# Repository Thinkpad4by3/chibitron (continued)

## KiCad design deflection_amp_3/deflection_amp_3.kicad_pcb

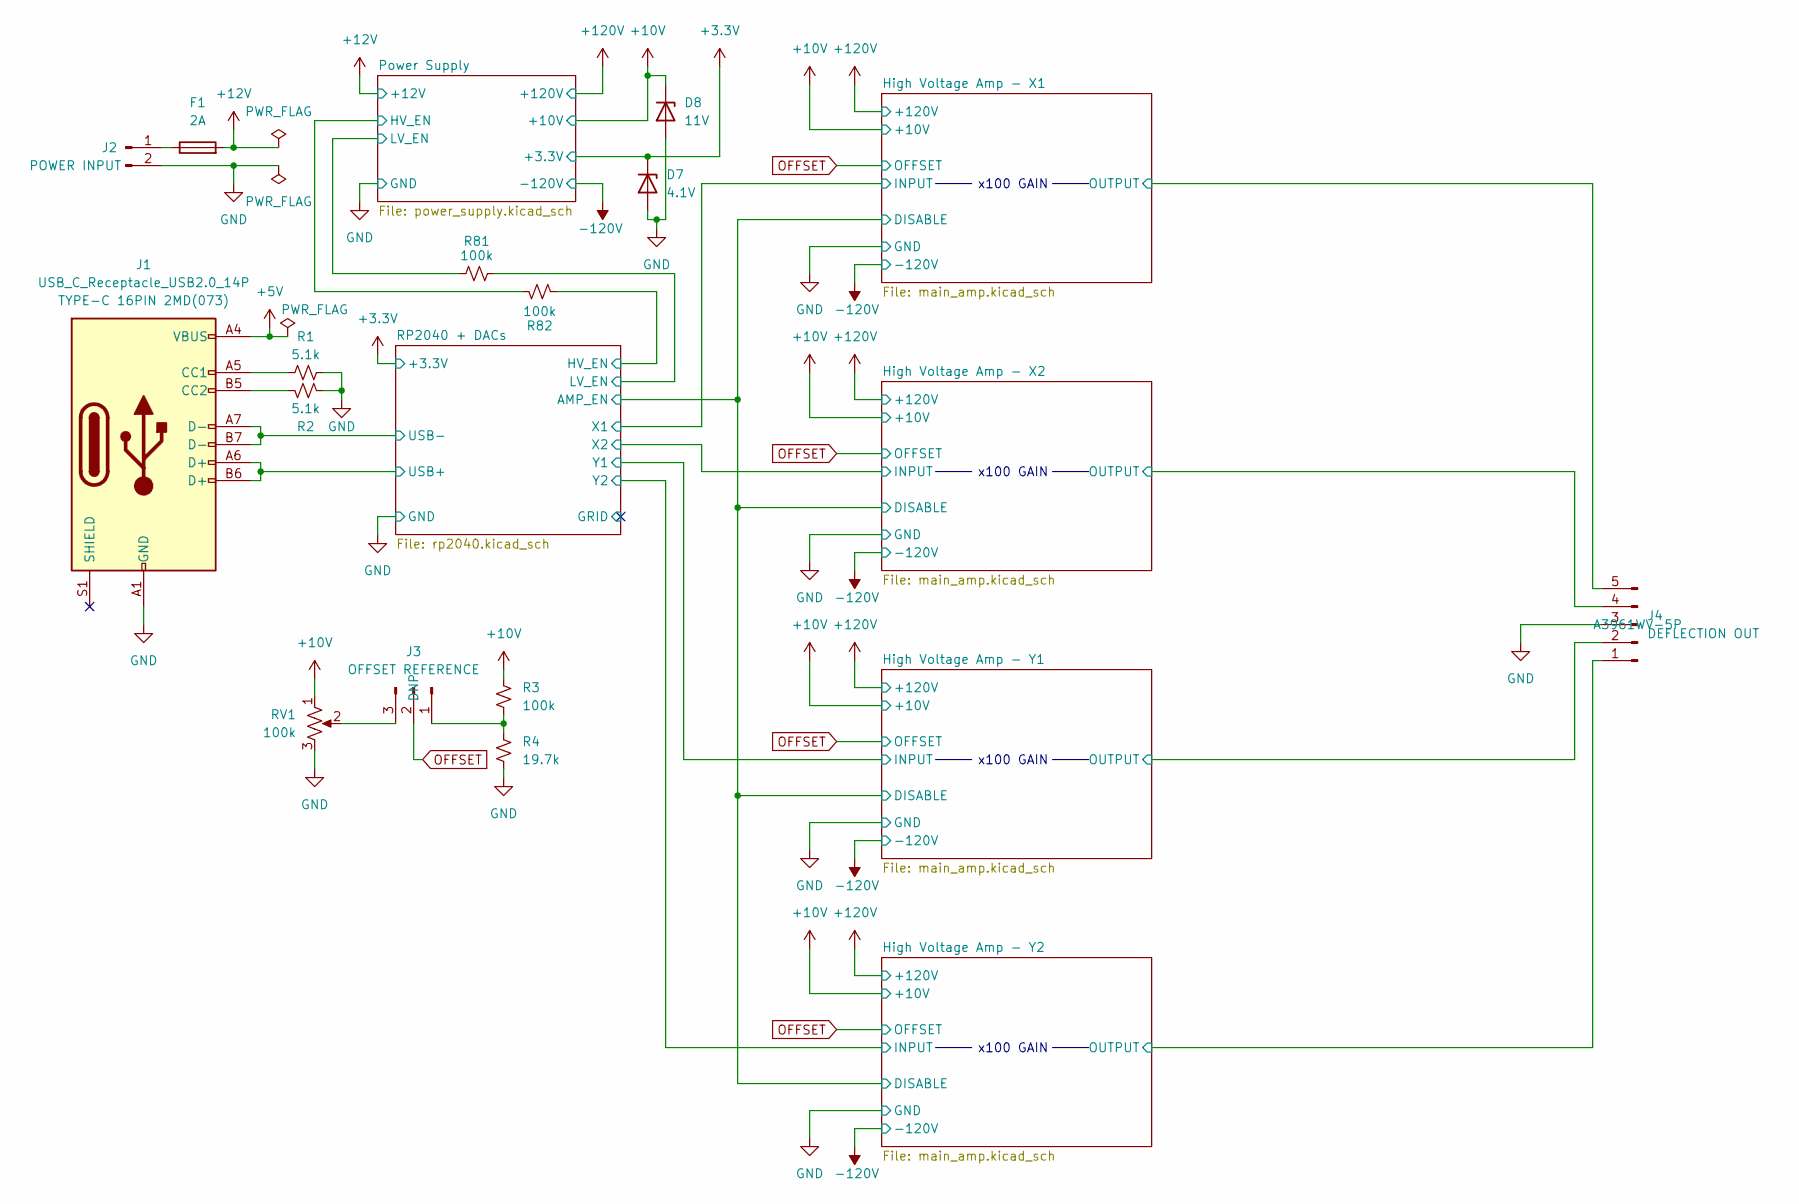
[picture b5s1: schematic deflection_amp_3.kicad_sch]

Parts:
D7: 4.1V; D_SOD-123; JLCPCB P/N BZT52C3V9
D8: 11V; D_SOD-123; JLCPCB P/N BZT52C11
F1: 2A; Fuse_0805_2012Metric; JLCPCB P/N MFU0805FF02000P500
J1: USB_C_Receptacle_USB2.0_14P; USB_C_Receptacle_Palconn_UTC16-G; Digikey P/N *check availabilty*
J2: POWER INPUT; Molex_KK-396_5273-02A_1x02_P3.96mm_Vertical; Digikey P/N 0009652028
J3: OFFSET REFERENCE; PinHeader_1x03_P2.54mm_Vertical; JLCPCB P/N DNP
J4: DEFLECTION OUT; Molex_KK-396_5273-05A_1x05_P3.96mm_Vertical; JLCPCB P/N A3961WV-5P
R1, R2: 5.1k; R_0603_1608Metric; Digikey P/N RC0603FR-075K1L
R3, R81, R82: 100k; R_0603_1608Metric; Digikey P/N RMCF0603FT100K
R4: 19.7k; R_0603_1608Metric; Digikey P/N *find new P/N for 19.7k*
RV1: 100k; Potentiometer_Bourns_3296W_Vertical; Digikey P/N 3361P-1-104GLF

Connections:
+3.3V: D7.1 (K); also elsewhere on the board
+5V: J1.A4 (VBUS), J1.A9 (VBUS), J1.B4 (VBUS), J1.B9 (VBUS)
+10V: D8.1 (K), R3.1, RV1.1; also elsewhere on the board
+12V: F1.2; also elsewhere on the board
/High Voltage Amp - X1/OUTPUT: J4.5; also elsewhere on the board
/High Voltage Amp - X2/OUTPUT: J4.4; also elsewhere on the board
/High Voltage Amp - Y1/OUTPUT: J4.2; also elsewhere on the board
/High Voltage Amp - Y2/OUTPUT: J4.1; also elsewhere on the board
/Power Supply/HV_EN: R82.2; also elsewhere on the board
/Power Supply/LV_EN: R81.1; also elsewhere on the board
/RP2040 + DACs/HV_EN: R82.1; also elsewhere on the board
/RP2040 + DACs/LV_EN: R81.2; also elsewhere on the board
/RP2040 + DACs/USB+: J1.A6 (D+), J1.B6 (D+); also elsewhere on the board
/RP2040 + DACs/USB-: J1.A7 (D-), J1.B7 (D-); also elsewhere on the board
GND: D7.2 (A), D8.2 (A), J1.A1 (GND), J1.A12 (GND), J1.B1 (GND), J1.B12 (GND), J2.2, J4.3, R1.2, R2.2, R4.2, RV1.3; also elsewhere on the board
unnamed: J1.A5 (CC1), R1.1
unnamed: J1.B5 (CC2), R2.1
unnamed: F1.1, J2.1
unnamed: J3.1, R3.2, R4.1
unnamed: J3.3, RV1.2
OFFSET: J3.2; also elsewhere on the board

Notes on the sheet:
x100 GAIN

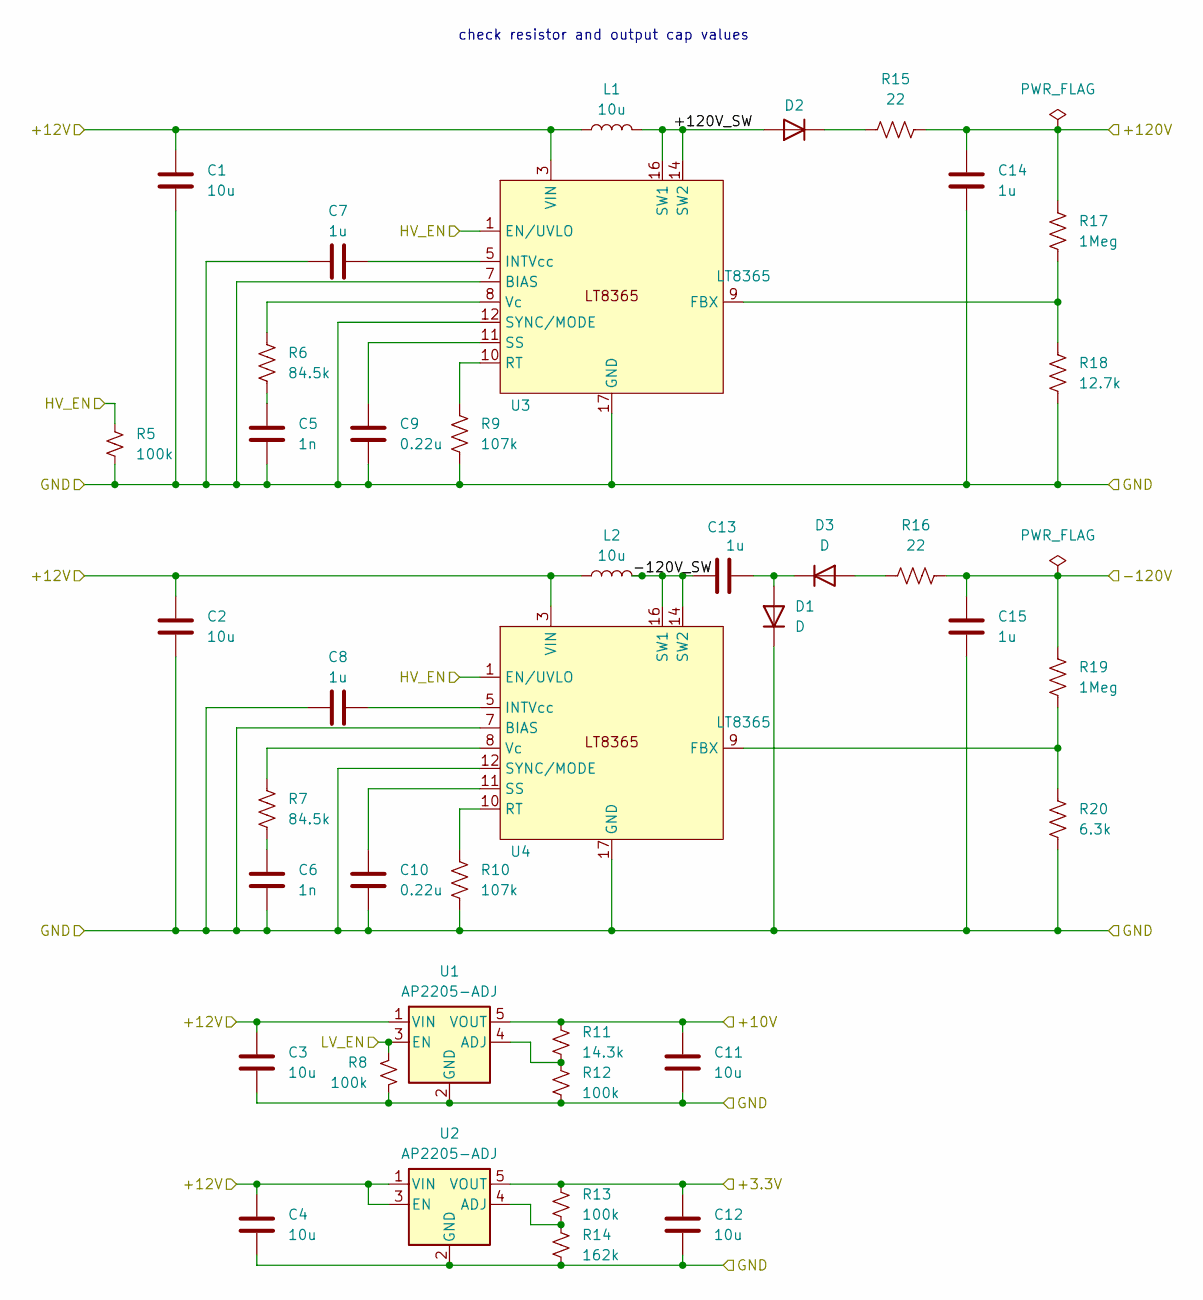
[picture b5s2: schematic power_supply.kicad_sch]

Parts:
C1, C2, C3, C4, C11, C12: 10u; C_0805_2012Metric; Digikey P/N CL21A106KAYNNNG
C5, C6: 1n; C_0603_1608Metric; Digikey P/N C0603C102K5RACTU
C7, C8: 1u; C_0603_1608Metric; Digikey P/N CL10A105KA8NNNC
C9, C10: 0.22u; C_0805_2012Metric; Digikey P/N C0805C224K5RACTU
C13, C14, C15: 1u; C_1812_4532Metric; Digikey P/N C5750X7R2E105K230KA
D1, D2, D3: D; D_SOD-123F; Digikey P/N MBR2H200SFT1G
L1, L2: 10u; L_APV_APH0420; Digikey P/N 74437324100
R5, R8, R12, R13: 100k; R_0603_1608Metric; Digikey P/N RMCF0603FT100K
R6, R7: 84.5k; R_0603_1608Metric; Digikey P/N RC0603FR-0784K5L
R9, R10: 107k; R_0603_1608Metric; Digikey P/N RC0603FR-07107KL
R11: 14.3k; R_0603_1608Metric; Digikey P/N RMCF0603FT14K3
R14: 162k; R_0603_1608Metric; Digikey P/N ERJ-3EKF1623V
R15, R16: 22; R_1206_3216Metric; Digikey P/N RV1206JR-0722ML
R17, R19: 1Meg; R_1206_3216Metric; Digikey P/N RNCS1206BKE1M00
R18: 12.7k; R_1206_3216Metric; Digikey P/N RMCF1206FT12K7
R20: 6.3k; R_1206_3216Metric; Digikey P/N RC1206FR-076K34L
U1, U2: AP2205-ADJ; SOT-23-5; Digikey P/N AP2205-W5-7
U3, U4: LT8365; Analog_MSOP-12-16-1EP_3x4.039mm_P0.5mm_EP1.651x2.845mm; Digikey P/N LT8365EMSE#TRPBF

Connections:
+3.3V: C12.1, R13.1, U2.5 (VOUT); also elsewhere on the board
+10V: C11.1, R11.1, U1.5 (VOUT); also elsewhere on the board
+12V: C1.1, C2.1, C3.1, C4.1, L1.1, L2.1, U1.1 (VIN), U2.1 (VIN), U2.3 (EN), U3.3 (VIN), U4.3 (VIN); also elsewhere on the board
+120V: C14.1, R15.2, R17.2; also elsewhere on the board
-120V: C15.1, R16.2, R19.2; also elsewhere on the board
/Power Supply/+120V_SW: D2.2 (A), L1.2, U3.14 (SW2), U3.16 (SW1)
/Power Supply/-120V_SW: C13.1, L2.2, U4.14 (SW2), U4.16 (SW1)
/Power Supply/HV_EN: R5.1, U3.1 (EN/UVLO), U4.1 (EN/UVLO); also elsewhere on the board
/Power Supply/LV_EN: R8.1, U1.3 (EN); also elsewhere on the board
GND: C1.2, C2.2, C3.2, C4.2, C5.2, C6.2, C7.1, C8.1, C9.2, C10.2, C11.2, C12.2, C14.2, C15.2, D1.1 (K), R5.2, R8.2, R9.2, R10.2, R12.2, R14.2, R18.1, R20.1, U1.2 (GND), U2.2 (GND), U3.7 (BIAS), U3.12 (SYNC/MODE), U3.17 (GND), U4.7 (BIAS), U4.12 (SYNC/MODE), U4.17 (GND); also elsewhere on the board
unnamed: C5.1, R6.2
unnamed: C6.1, R7.2
unnamed: C13.2, D1.2 (A), D3.1 (K)
unnamed: D2.1 (K), R15.1
unnamed: D3.2 (A), R16.1
unnamed: R11.2, R12.1, U1.4 (ADJ)
unnamed: R13.2, R14.1, U2.4 (ADJ)
unnamed: R17.1, R18.2, U3.9 (FBX)
unnamed: C7.2, U3.5 (INTVcc)
unnamed: R9.1, U3.10 (RT)
unnamed: C9.1, U3.11 (SS)
unnamed: R6.1, U3.8 (Vc)
unnamed: R19.1, R20.2, U4.9 (FBX)
unnamed: C8.2, U4.5 (INTVcc)
unnamed: R10.1, U4.10 (RT)
unnamed: C10.1, U4.11 (SS)
unnamed: R7.1, U4.8 (Vc)

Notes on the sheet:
check resistor and output cap values

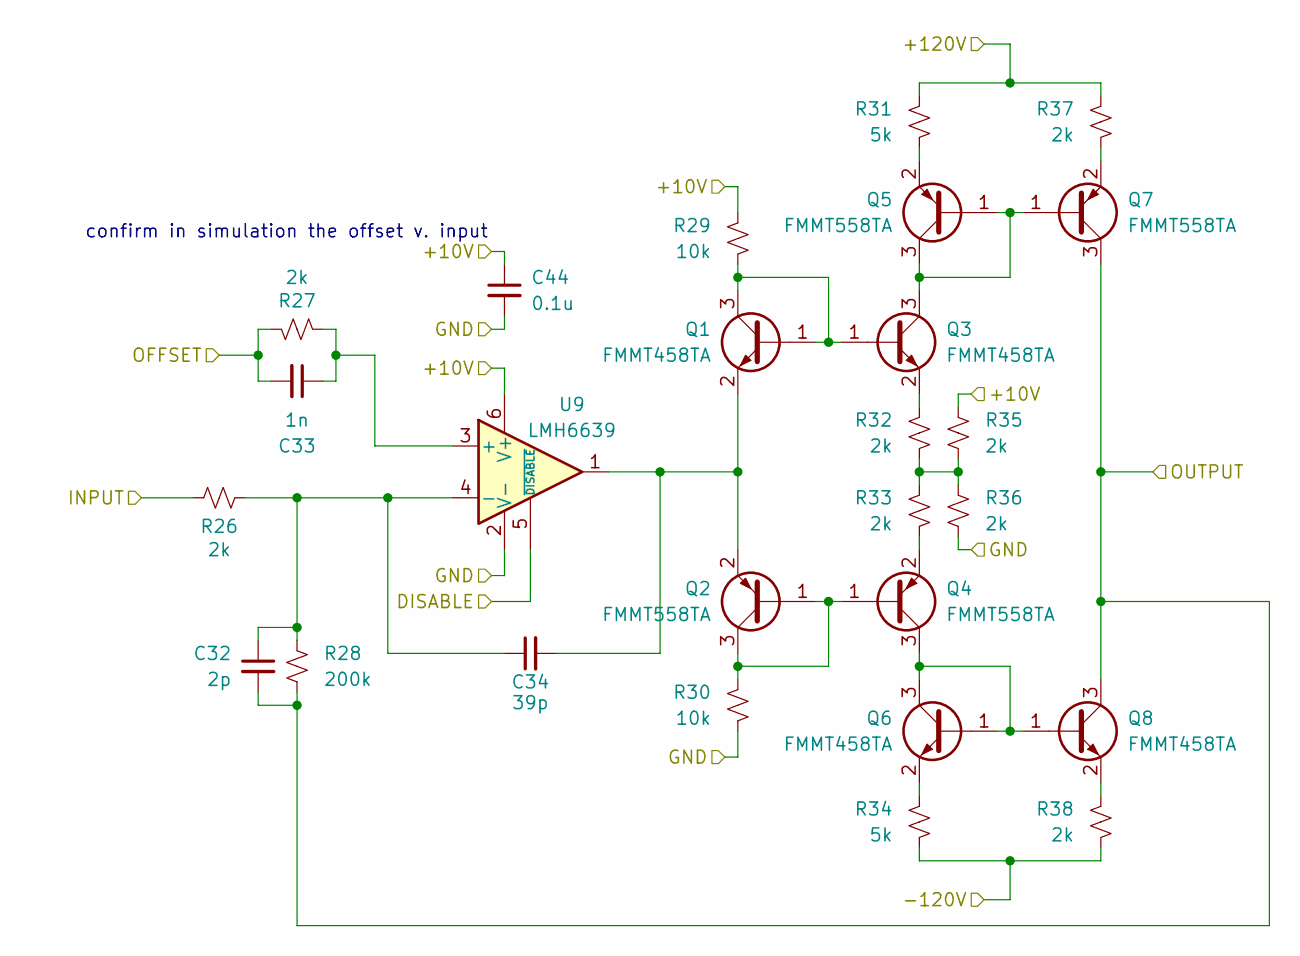
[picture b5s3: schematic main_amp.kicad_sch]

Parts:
C32: 2p; C_0603_1608Metric; Digikey P/N QSCP251Q2R0B1GV001T
C33: 1n; C_0603_1608Metric; Digikey P/N C0603C102K5RACTU
C34: 39p; C_0603_1608Metric; Digikey P/N QSCP251Q390G1GV001T
C44: 0.1u; C_0603_1608Metric; Digikey P/N C0603C104K5RAC7411
Q1, Q3, Q6, Q8: FMMT458TA; SOT-23; Digikey P/N FMMT458TA
Q2, Q4, Q5, Q7: FMMT558TA; SOT-23; Digikey P/N FMMT558TA
R26, R27, R32, R33, R35, R36, R37, R38: 2k; R_1206_3216Metric; Digikey P/N RMCF1206FT2K00
R28: 200k; R_1206_3216Metric; Digikey P/N RC1206JR-07200KL
R29, R30: 10k; R_0603_1608Metric; Digikey P/N RC0603FR-0710KL
R31, R34: 5k; R_1206_3216Metric; Digikey P/N RT1206FRE075KL
U9: LMH6639; TSOT-23-6; Digikey P/N LMH6639MFX/NOPB

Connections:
+10V: C44.1, R29.1, R35.1, U9.6 (V+); also elsewhere on the board
+120V: R31.1, R37.1; also elsewhere on the board
-120V: R34.2, R38.2; also elsewhere on the board
/High Voltage Amp - X1/DISABLE: U9.5 (~DISABLE); also elsewhere on the board
/High Voltage Amp - X1/INPUT: R26.2; also elsewhere on the board
/High Voltage Amp - X1/OUTPUT: C32.2, Q7.3 (C), Q8.3 (C), R28.2; also elsewhere on the board
GND: C44.2, R30.2, R36.2, U9.2 (V-); also elsewhere on the board
unnamed: Q1.1 (B), Q1.3 (C), Q3.1 (B), R29.2
unnamed: C34.2, Q1.2 (E), Q2.2 (E), U9.1
unnamed: Q2.1 (B), Q2.3 (C), Q4.1 (B), R30.1
unnamed: Q3.3 (C), Q5.1 (B), Q5.3 (C), Q7.1 (B)
unnamed: Q3.2 (E), R32.1
unnamed: Q4.3 (C), Q6.1 (B), Q6.3 (C), Q8.1 (B)
unnamed: Q4.2 (E), R33.2
unnamed: Q5.2 (E), R31.2
unnamed: Q6.2 (E), R34.1
unnamed: Q7.2 (E), R37.2
unnamed: Q8.2 (E), R38.1
unnamed: R32.2, R33.1, R35.2, R36.1
unnamed: C33.1, R27.1, U9.3 (+)
unnamed: C32.1, C34.1, R26.1, R28.1, U9.4 (-)
OFFSET: C33.2, R27.2; also elsewhere on the board

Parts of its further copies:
C35, C38, C41: 2p; C_0603_1608Metric; Digikey P/N QSCP251Q2R0B1GV001T
C36, C39, C42: 1n; C_0603_1608Metric; Digikey P/N C0603C102K5RACTU
C37, C40, C43: 39p; C_0603_1608Metric; Digikey P/N QSCP251Q390G1GV001T
C45, C46, C47: 0.1u; C_0603_1608Metric; Digikey P/N C0603C104K5RAC7411
Q9, Q11, Q14, Q16, Q17, Q19, Q22, Q24, Q25, Q27, Q30, Q32: FMMT458TA; SOT-23; Digikey P/N FMMT458TA
Q10, Q12, Q13, Q15, Q18, Q20, Q21, Q23, Q26, Q28, Q29, Q31: FMMT558TA; SOT-23; Digikey P/N FMMT558TA
R39, R40, R45, R46, R48, R49, R50, R51, R52, R53, R58, R59, R61, R62, R63, R64, R65, R66, R71, R72, R74, R75, R76, R77: 2k; R_1206_3216Metric; Digikey P/N RMCF1206FT2K00
R41, R54, R67: 200k; R_1206_3216Metric; Digikey P/N RC1206JR-07200KL
R42, R43, R55, R56, R68, R69: 10k; R_0603_1608Metric; Digikey P/N RC0603FR-0710KL
R44, R47, R57, R60, R70, R73: 5k; R_1206_3216Metric; Digikey P/N RT1206FRE075KL
U10, U11, U12: LMH6639; TSOT-23-6; Digikey P/N LMH6639MFX/NOPB

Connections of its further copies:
+10V: C45.1, C46.1, C47.1, R42.1, R48.1, R55.1, R61.1, R68.1, R74.1, U10.6 (V+), U11.6 (V+), U12.6 (V+); also elsewhere on the board
+120V: R44.1, R50.1, R57.1, R63.1, R70.1, R76.1; also elsewhere on the board
-120V: R47.2, R51.2, R60.2, R64.2, R73.2, R77.2; also elsewhere on the board
/High Voltage Amp - X1/DISABLE: U10.5 (~DISABLE), U11.5 (~DISABLE), U12.5 (~DISABLE); also elsewhere on the board
/High Voltage Amp - X2/INPUT: R39.2; also elsewhere on the board
/High Voltage Amp - X2/OUTPUT: C35.2, Q15.3 (C), Q16.3 (C), R41.2; also elsewhere on the board
/High Voltage Amp - Y1/INPUT: R52.2; also elsewhere on the board
/High Voltage Amp - Y1/OUTPUT: C38.2, Q23.3 (C), Q24.3 (C), R54.2; also elsewhere on the board
/High Voltage Amp - Y2/INPUT: R65.2; also elsewhere on the board
/High Voltage Amp - Y2/OUTPUT: C41.2, Q31.3 (C), Q32.3 (C), R67.2; also elsewhere on the board
GND: C45.2, C46.2, C47.2, R43.2, R49.2, R56.2, R62.2, R69.2, R75.2, U10.2 (V-), U11.2 (V-), U12.2 (V-); also elsewhere on the board
unnamed: Q10.1 (B), Q10.3 (C), Q12.1 (B), R43.1
unnamed: C37.2, Q9.2 (E), Q10.2 (E), U10.1
unnamed: Q9.1 (B), Q9.3 (C), Q11.1 (B), R42.2
unnamed: Q11.3 (C), Q13.1 (B), Q13.3 (C), Q15.1 (B)
unnamed: Q11.2 (E), R45.1
unnamed: Q12.3 (C), Q14.1 (B), Q14.3 (C), Q16.1 (B)
unnamed: Q12.2 (E), R46.2
unnamed: Q13.2 (E), R44.2
unnamed: Q14.2 (E), R47.1
unnamed: Q15.2 (E), R50.2
unnamed: Q16.2 (E), R51.1
unnamed: Q17.1 (B), Q17.3 (C), Q19.1 (B), R55.2
unnamed: C40.2, Q17.2 (E), Q18.2 (E), U11.1
unnamed: Q18.1 (B), Q18.3 (C), Q20.1 (B), R56.1
unnamed: Q19.3 (C), Q21.1 (B), Q21.3 (C), Q23.1 (B)
unnamed: Q19.2 (E), R58.1
unnamed: Q20.3 (C), Q22.1 (B), Q22.3 (C), Q24.1 (B)
unnamed: Q20.2 (E), R59.2
unnamed: Q21.2 (E), R57.2
unnamed: Q22.2 (E), R60.1
unnamed: Q23.2 (E), R63.2
unnamed: Q24.2 (E), R64.1
unnamed: Q25.1 (B), Q25.3 (C), Q27.1 (B), R68.2
unnamed: C43.2, Q25.2 (E), Q26.2 (E), U12.1
unnamed: Q26.1 (B), Q26.3 (C), Q28.1 (B), R69.1
unnamed: Q27.3 (C), Q29.1 (B), Q29.3 (C), Q31.1 (B)
unnamed: Q27.2 (E), R71.1
unnamed: Q28.3 (C), Q30.1 (B), Q30.3 (C), Q32.1 (B)
unnamed: Q28.2 (E), R72.2
unnamed: Q29.2 (E), R70.2
unnamed: Q30.2 (E), R73.1
unnamed: Q31.2 (E), R76.2
unnamed: Q32.2 (E), R77.1
unnamed: R45.2, R46.1, R48.2, R49.1
unnamed: R58.2, R59.1, R61.2, R62.1
unnamed: R71.2, R72.1, R74.2, R75.1
unnamed: C36.1, R40.1, U10.3 (+)
unnamed: C35.1, C37.1, R39.1, R41.1, U10.4 (-)
unnamed: C39.1, R53.1, U11.3 (+)
unnamed: C38.1, C40.1, R52.1, R54.1, U11.4 (-)
unnamed: C42.1, R66.1, U12.3 (+)
unnamed: C41.1, C43.1, R65.1, R67.1, U12.4 (-)
OFFSET: C36.2, C39.2, C42.2, R40.2, R53.2, R66.2; also elsewhere on the board

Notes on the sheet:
confirm in simulation the offset v. input

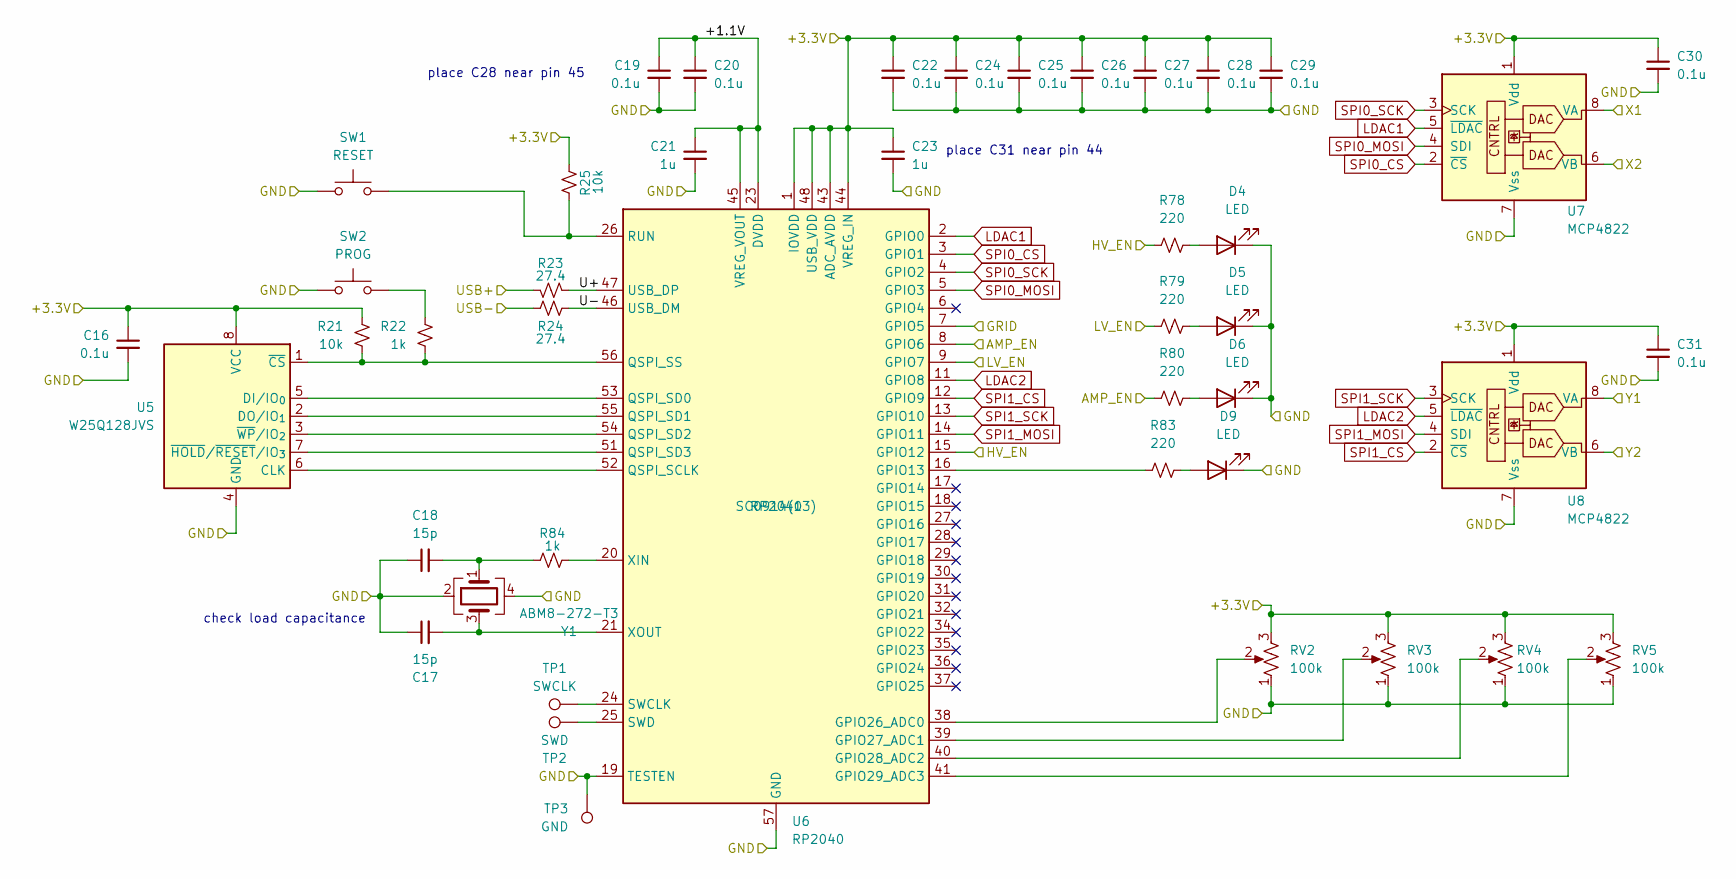
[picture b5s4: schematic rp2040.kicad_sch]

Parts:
C16, C19, C20, C22, C24, C25, C26, C27, C28, C29, C30, C31: 0.1u; C_0603_1608Metric; Digikey P/N C0603C104K5RAC7411
C17, C18: 15p; C_0603_1608Metric; Digikey P/N 600S150JT250XT4K
C21, C23: 1u; C_0603_1608Metric; Digikey P/N CL10A105KA8NNNC
D4, D5, D6, D9: LED; LED_0603_1608Metric; JLCPCB P/N KT-0603R
R21, R25: 10k; R_0603_1608Metric; Digikey P/N RC0603FR-0710KL
R22, R84: 1k; R_0603_1608Metric; Digikey P/N *find p/n*
R23, R24: 27.4; R_0603_1608Metric; Digikey P/N *find p/n*
R78, R79, R80, R83: 220; R_0603_1608Metric; JLCPCB P/N 0603WAF2400T5E
RV2: 100k; Potentiometer_Bourns_3296W_Vertical; Digikey P/N 3296W-1-104
RV3, RV4, RV5: 100k; Potentiometer_Bourns_3296W_Vertical; Digikey P/N 3361P-1-104GLF
SW1: RESET; SW_SPST_Omron_B3FS-101xP; Digikey P/N B3FS-1012P
SW2: PROG; SW_SPST_Omron_B3FS-101xP; Digikey P/N B3FS-1012P
TP1: SWCLK; TestPoint_Pad_1.0x1.0mm
TP2: SWD; TestPoint_Pad_1.0x1.0mm
TP3: GND; TestPoint_Pad_1.0x1.0mm
U5: W25Q128JVS; SOIC-8_5.3x5.3mm_P1.27mm; JLCPCB P/N W25Q128JVSIQ
U6: RP2040; QFN-56-1EP_7x7mm_P0.4mm_EP3.2x3.2mm; Digikey P/N SC0914(13)
U7, U8: MCP4822; SOIC127P599X175-8N; Digikey P/N MCP4822-E/SN
Y1: ABM8-272-T3; Crystal_SMD_3225-4Pin_3.2x2.5mm; Digikey P/N ABM8-272-T3

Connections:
+3.3V: C16.1, C22.1, C23.1, C24.1, C25.1, C26.1, C27.1, C28.1, C29.1, C30.1, C31.1, R21.1, R25.2, RV2.3, RV3.3, RV4.3, RV5.3, U5.8 (VCC), U6.1 (IOVDD), U6.10 (IOVDD), U6.22 (IOVDD), U6.33 (IOVDD), U6.42 (IOVDD), U6.43 (ADC_AVDD), U6.44 (VREG_IN), U6.48 (USB_VDD), U6.49 (IOVDD), U7.1 (Vdd), U8.1 (Vdd); also elsewhere on the board
/High Voltage Amp - X1/DISABLE: R80.1, U6.8 (GPIO6); also elsewhere on the board
/High Voltage Amp - X1/INPUT: U7.8 (VA); also elsewhere on the board
/High Voltage Amp - X2/INPUT: U7.6 (VB); also elsewhere on the board
/High Voltage Amp - Y1/INPUT: U8.8 (VA); also elsewhere on the board
/High Voltage Amp - Y2/INPUT: U8.6 (VB); also elsewhere on the board
/RP2040 + DACs/+1.1V: C19.1, C20.1, C21.1, U6.23 (DVDD), U6.45 (VREG_VOUT), U6.50 (DVDD)
/RP2040 + DACs/GRID: U6.7 (GPIO5)
/RP2040 + DACs/HV_EN: R78.1, U6.15 (GPIO12); also elsewhere on the board
/RP2040 + DACs/LV_EN: R79.1, U6.9 (GPIO7); also elsewhere on the board
/RP2040 + DACs/U+: R23.2, U6.47 (USB_DP)
/RP2040 + DACs/U-: R24.2, U6.46 (USB_DM)
/RP2040 + DACs/USB+: R23.1; also elsewhere on the board
/RP2040 + DACs/USB-: R24.1; also elsewhere on the board
GND: C16.2, C17.1, C18.1, C19.2, C20.2, C21.2, C22.2, C23.2, C24.2, C25.2, C26.2, C27.2, C28.2, C29.2, C30.2, C31.2, D4.1 (K), D5.1 (K), D6.1 (K), D9.1 (K), RV2.1, RV3.1, RV4.1, RV5.1, SW1.1, SW2.1, TP3.1, U5.4 (GND), U6.19 (TESTEN), U6.57 (GND), U7.7 (Vss), U8.7 (Vss), Y1.2, Y1.4; also elsewhere on the board
LDAC1: U6.2 (GPIO0), U7.5 (~LDAC)
LDAC2: U6.11 (GPIO8), U8.5 (~LDAC)
unnamed: C18.2, R84.1, Y1.1
unnamed: D4.2 (A), R78.2
unnamed: D5.2 (A), R79.2
unnamed: D6.2 (A), R80.2
unnamed: D9.2 (A), R83.2
unnamed: R22.1, SW2.2
unnamed: U5.6 (CLK), U6.52 (QSPI_SCLK)
unnamed: U5.5 (DI/IO_{0}), U6.53 (QSPI_SD0)
unnamed: U5.2 (DO/IO_{1}), U6.55 (QSPI_SD1)
unnamed: R21.2, R22.2, U5.1 (~CS), U6.56 (QSPI_SS)
unnamed: U5.7 (~HOLD/~RESET/IO_{3}), U6.51 (QSPI_SD3)
unnamed: U5.3 (~WP/IO_{2}), U6.54 (QSPI_SD2)
unnamed: R83.1, U6.16 (GPIO13)
unnamed: RV2.2, U6.38 (GPIO26_ADC0)
unnamed: RV3.2, U6.39 (GPIO27_ADC1)
unnamed: RV4.2, U6.40 (GPIO28_ADC2)
unnamed: RV5.2, U6.41 (GPIO29_ADC3)
unnamed: R25.1, SW1.2, U6.26 (RUN)
unnamed: TP1.1, U6.24 (SWCLK)
unnamed: TP2.1, U6.25 (SWD)
unnamed: R84.2, U6.20 (XIN)
unnamed: C17.2, U6.21 (XOUT), Y1.3
SPI0_CS: U6.3 (GPIO1), U7.2 (~CS)
SPI0_MOSI: U6.5 (GPIO3), U7.4 (SDI)
SPI0_SCK: U6.4 (GPIO2), U7.3 (SCK)
SPI1_CS: U6.12 (GPIO9), U8.2 (~CS)
SPI1_MOSI: U6.14 (GPIO11), U8.4 (SDI)
SPI1_SCK: U6.13 (GPIO10), U8.3 (SCK)

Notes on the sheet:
place C28 near pin 45
place C31 near pin 44
check load capacitance

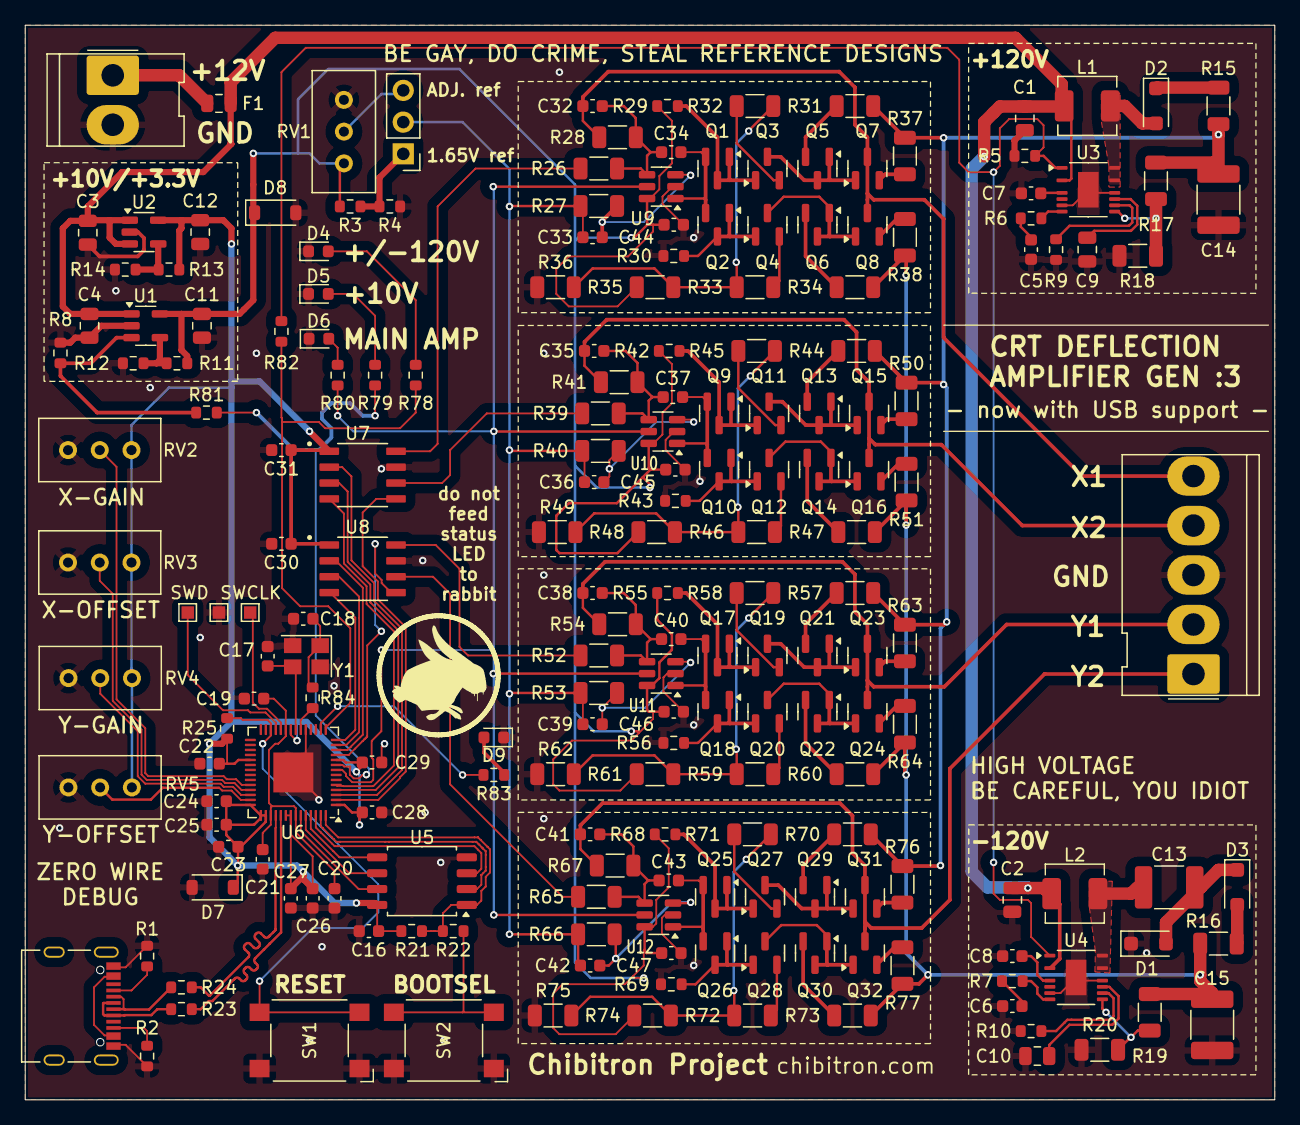
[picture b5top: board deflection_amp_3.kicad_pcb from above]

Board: 2 copper layers, 100.0 x 86.0 mm, 202 parts (0 on the bottom side), 136 nets.

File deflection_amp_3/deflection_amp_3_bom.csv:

"Value","Reference","Footprint","JLCPCB P/N"
"POWER INPUT","J2","Connector_Molex:Molex_KK-396_5273-02A_1x02_P3.96mm_Vertical",""
"OFFSET REFERENCE","J3","Connector_PinHeader_2.54mm:PinHeader_1x03_P2.54mm_Vertical",""
"DEFLECTION OUT","J4","Connector_Molex:Molex_KK-396_5273-05A_1x05_P3.96mm_Vertical",""
"2p","C32,C35,C38,C41","Capacitor_SMD:C_0603_1608Metric","0603CG2R0C500NT"
"39p","C34,C37,C40,C43","Capacitor_SMD:C_0603_1608Metric","0603CG390J500NT"
"1k","R22","Resistor_SMD:R_0603_1608Metric","0603WAF1001T5E"
"10k","R21,R25,R29,R30,R42,R43,R55,R56,R68,R69","Resistor_SMD:R_0603_1608Metric","0603WAF1002T5E"
"100k","R3,R5,R8,R12,R13","Resistor_SMD:R_0603_1608Metric","0603WAF1003T5E"
"107k","R9,R10","Resistor_SMD:R_0603_1608Metric","0603WAF1103T5E"
"14.3k","R11","Resistor_SMD:R_0603_1608Metric","0603WAF1502T5E"
"162k","R14","Resistor_SMD:R_0603_1608Metric","0603WAF1603T5E"
"19.7k","R4","Resistor_SMD:R_0603_1608Metric","0603WAF2002T5E"
"220","R78,R79,R80","Resistor_SMD:R_0603_1608Metric","0603WAF2400T5E"
"27.4","R23,R24","Resistor_SMD:R_0603_1608Metric","0603WAF270JT5E"
"5.1k","R1,R2","Resistor_SMD:R_0603_1608Metric","0603WAF5101T5E"
"84.5k","R6,R7","Resistor_SMD:R_0603_1608Metric","0603WAF8202T5E"
"1Meg","R17,R19","Resistor_SMD:R_1206_3216Metric","1206W4F1004T5E"
"2k","R26,R27,R32,R33,R35,R36,R37,R38,R39,R40,R45,R46,R48,R49,R50,R51,R52,R53,R58,R59,R61,R62,R63,R64,R65,R66,R71,R72,R74,R75,R76,R77","Resistor_SMD:R_1206_3216Metric","1206W4F2001T5E"
"200k","R28,R41,R54,R67","Resistor_SMD:R_1206_3216Metric","1206W4F2003T5E"
"22","R15,R16","Resistor_SMD:R_1206_3216Metric","1206W4F220JT5E"
"5k","R31,R34,R44,R47,R57,R60,R70,R73","Resistor_SMD:R_1206_3216Metric","1206W4F5101T5E"
"6.3k","R20","Resistor_SMD:R_1206_3216Metric","1206W4F6201T5E"
"12.7k","R18","Resistor_SMD:R_1206_3216Metric","1206W4J0133T5E"
"100k","RV1,RV2,RV3,RV4,RV5","Potentiometer_SMD:Potentiometer_Vishay_TS53YJ_Vertical","3296W-1-104"
"ABM8-272-T3","Y1","Crystal:Crystal_SMD_3225-4Pin_3.2x2.5mm","ABM8-272-T3"
"AP2205-ADJ","U1,U2","Package_TO_SOT_SMD:SOT-23-5","AP2205-W5-7"
"RESET","SW1","Button_Switch_SMD:SW_SPST_Omron_B3FS-101xP","B3FS-1012P"
"PROG","SW2","Button_Switch_SMD:SW_SPST_Omron_B3FS-101xP","B3FS-1012P"
"1u","C7,C8,C21,C23","Capacitor_SMD:C_0603_1608Metric","CL10A105KB8NNNC"
"1n","C5,C6,C33,C36,C39,C42","Capacitor_SMD:C_0603_1608Metric","CL10B102KB8NNNC"
"0.1u","C16,C19,C20,C22,C24,C25,C26,C27,C28,C29,C30,C31,C44,C45,C46,C47","Capacitor_SMD:C_0603_1608Metric","CL10B104KA8NNNC"
"15p","C17,C18","Capacitor_SMD:C_0603_1608Metric","CL10C150JB8NNNC"
"10u","C1,C2,C3,C4,C11,C12","Capacitor_SMD:C_0805_2012Metric","CL21A106KAYNNNE"
"0.22u","C9,C10","Capacitor_SMD:C_0805_2012Metric","CL21B224KBFNNNE"
"MCP4822","U7,U8","Package_SO:SOIC-8_5.3x5.3mm_P1.27mm","double check footprint"
"D","D1,D2,D3","Diode_SMD:D_SOD-123F","DSK320"
"USB_C_Receptacle_USB2.0_14P","J1","Connector_USB:USB_C_Receptacle_JAE_DX07S016JA1R1500","DX07S016JA1R1500"
"FMMT458TA","Q1,Q3,Q6,Q8,Q9,Q11,Q14,Q16,Q17,Q19,Q22,Q24,Q25,Q27,Q30,Q32","Package_TO_SOT_SMD:SOT-23","FMMT458QTA"
"FMMT558TA","Q2,Q4,Q5,Q7,Q10,Q12,Q13,Q15,Q18,Q20,Q21,Q23,Q26,Q28,Q29,Q31","Package_TO_SOT_SMD:SOT-23","FMMT558QTA"
"1u","C13,C14,C15","Capacitor_SMD:C_2220_5750Metric","FS55X105K251EGG"
"10u","L1,L2","Inductor_SMD:L_APV_APH0420","FXL0420-100-M"
"LED","D4,D5,D6","LED_SMD:LED_0603_1608Metric","KT-0603R"
"LMH6639","U9,U10,U11,U12","Package_TO_SOT_SMD:TSOT-23-6","LMH6639MFX/NOPB"
"LT8365","U3,U4","Package_SO:Analog_MSOP-12-16-1EP_3x4.039mm_P0.5mm_EP1.651x2.845mm","LT8365EMSE#TRPBF"
"2A","F1","Fuse:Fuse_0805_2012Metric","MFU0805FF02000P100"
"RP2040","U6","Package_DFN_QFN:QFN-56-1EP_7x7mm_P0.4mm_EP3.2x3.2mm","SC0914(13)"
"W25Q128JVS","U5","Package_SO:SOIC-8_5.3x5.3mm_P1.27mm","W25Q128JVSIQ"

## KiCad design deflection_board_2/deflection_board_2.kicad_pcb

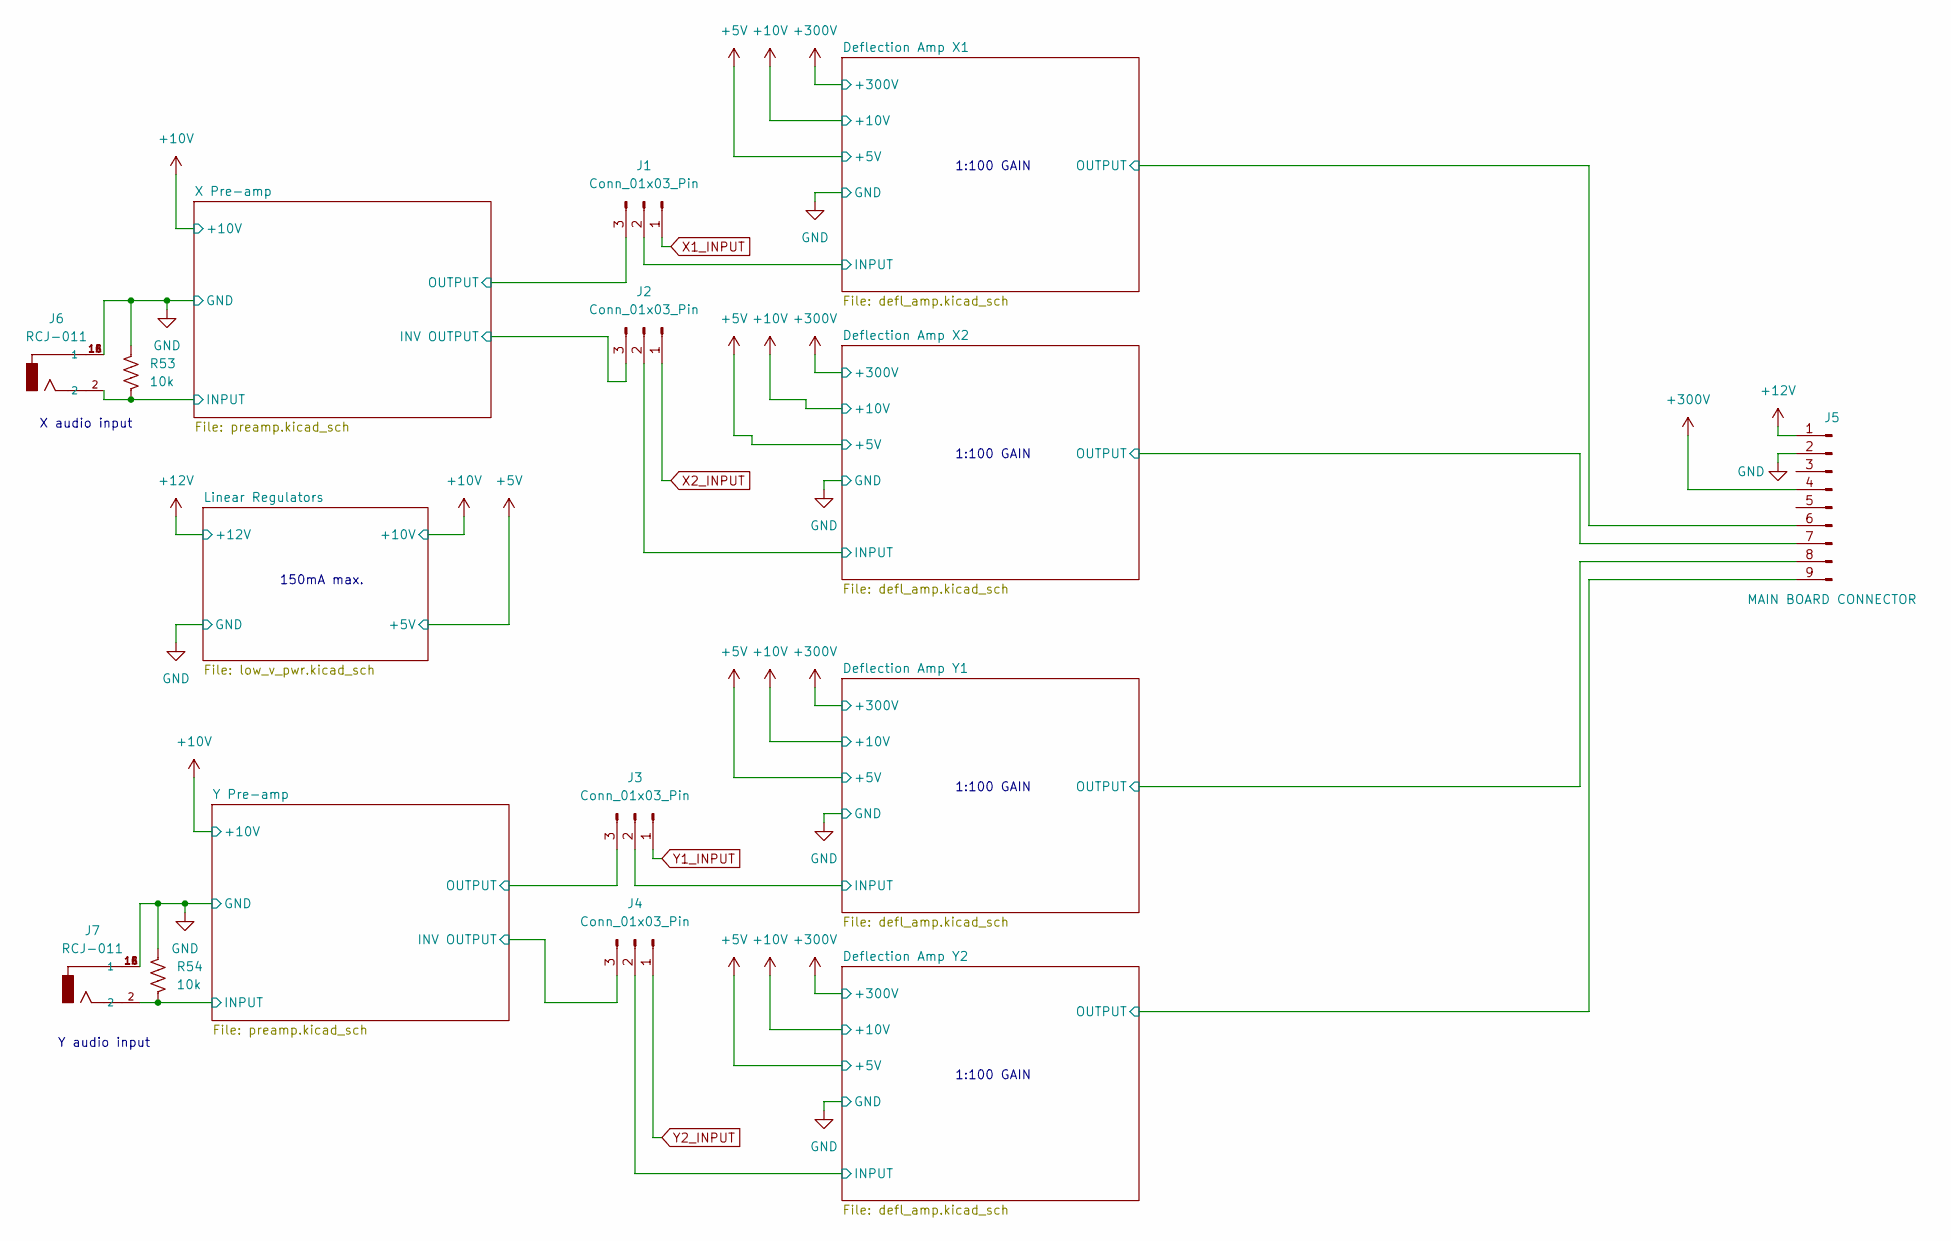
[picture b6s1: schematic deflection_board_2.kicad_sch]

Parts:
J1, J2, J3, J4: Conn_01x03_Pin; PinHeader_1x03_P2.54mm_Vertical
J5: MAIN BOARD CONNECTOR; Molex_KK-396_5273-09A_1x09_P3.96mm_Vertical
J6, J7: RCJ-011; CUI_RCJ-011; PART_REV B
R53, R54: 10k; R_0603_1608Metric

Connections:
+12V: J5.1; also elsewhere on the board
+300V: J5.4; also elsewhere on the board
/Deflection Amp X1/INPUT: J1.2; also elsewhere on the board
/Deflection Amp X1/OUTPUT: J5.6; also elsewhere on the board
/Deflection Amp X2/INPUT: J2.2; also elsewhere on the board
/Deflection Amp X2/OUTPUT: J5.7; also elsewhere on the board
/Deflection Amp Y1/INPUT: J3.2; also elsewhere on the board
/Deflection Amp Y1/OUTPUT: J5.8; also elsewhere on the board
/Deflection Amp Y2/INPUT: J4.2; also elsewhere on the board
/Deflection Amp Y2/OUTPUT: J5.9; also elsewhere on the board
/X Pre-amp/INPUT: J6.2, R53.2; also elsewhere on the board
/X Pre-amp/INV OUTPUT: J2.3; also elsewhere on the board
/X Pre-amp/OUTPUT: J1.3; also elsewhere on the board
/Y Pre-amp/INPUT: J7.2, R54.2; also elsewhere on the board
/Y Pre-amp/INV OUTPUT: J4.3; also elsewhere on the board
/Y Pre-amp/OUTPUT: J3.3; also elsewhere on the board
GND: J5.2, J6.1A (1), J6.1B (1), J6.1C (1), J7.1A (1), J7.1B (1), J7.1C (1), R53.1, R54.1; also elsewhere on the board
X1_INPUT: J1.1
X2_INPUT: J2.1
Y1_INPUT: J3.1
Y2_INPUT: J4.1

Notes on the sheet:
1:100 GAIN
Y audio input
150mA max.
X audio input
